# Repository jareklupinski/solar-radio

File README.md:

# solar-radio
A dev module for experimenting with low-power FM designs

The SI4825 is an interesting chip, so I made an easy to interface board for prototyping a few ideas I had.

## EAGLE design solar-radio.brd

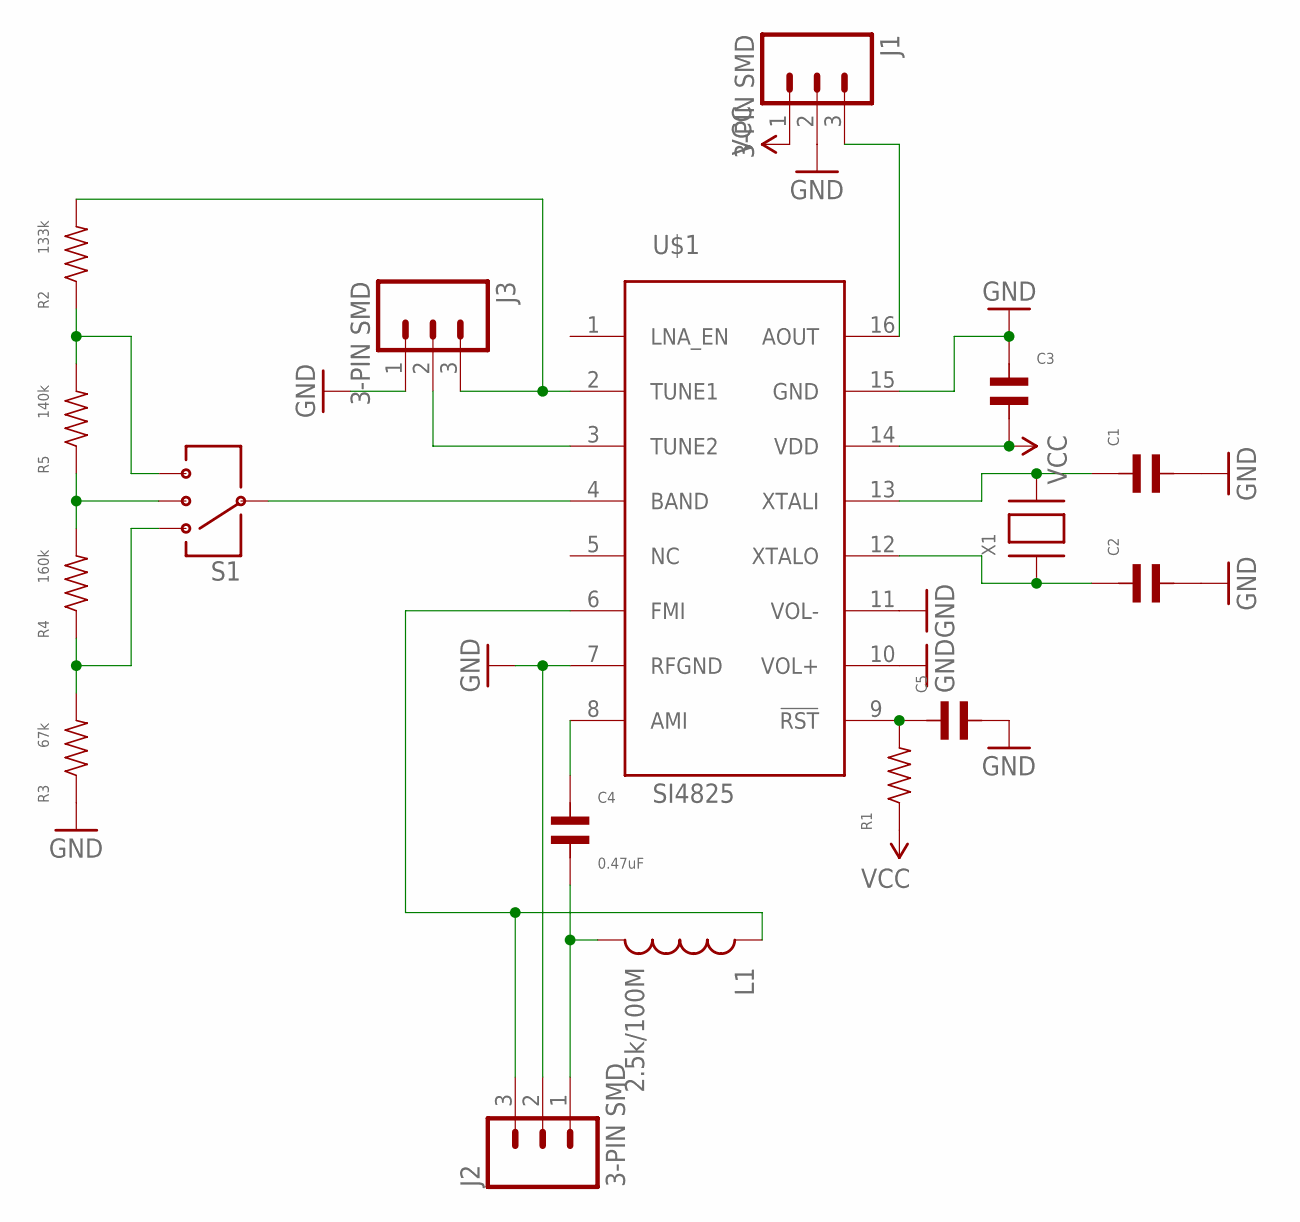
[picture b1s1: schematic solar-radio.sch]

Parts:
C1, C2, C3, C5: CAPACITOR_NP_0805; C0805
C4: 0.47uF; C0805
J1, J2, J3: 3-PIN SMD; JST-3-SMD
L1: 2.5k/100M; 0805
R1: RESISTOR_0805; R0805
R2: 133k; R0805
R3: 67k; R0805
R4: 160k; R0805
R5: 140k; R0805
S1: SWITCH-SP3T; SWITCH-SP3T-SMD
U$1: SI4825; SOIC16N
X1: XTAL-3.2X1.5; XTAL3215

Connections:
GND: C1.P$2, C2.P$2, C3.P$1, C5.P$2, J1.2, J2.2, J3.1, R3.P$1, U$1.7 (RFGND), U$1.10 (VOL+), U$1.11 (VOL-), U$1.15 (GND)
unnamed: J3.2, U$1.3 (TUNE2)
unnamed: J3.3, R2.P$2, U$1.2 (TUNE1)
unnamed: R2.P$1, R5.P$2, S1.4
unnamed: R4.P$2, R5.P$1, S1.2
unnamed: R3.P$2, R4.P$1, S1.1
unnamed: S1.3, U$1.4 (BAND)
unnamed: C4.P$1, U$1.8 (AMI)
unnamed: C4.P$2, J2.1, L1.2
unnamed: J2.3, L1.1, U$1.6 (FMI)
unnamed: C5.P$1, R1.P$2, U$1.9 (!RST)
unnamed: C1.P$1, U$1.13 (XTALI), X1.P$2
unnamed: C2.P$1, U$1.12 (XTALO), X1.P$1
unnamed: J1.3, U$1.16 (AOUT)
VCC: C3.P$2, J1.1, R1.P$1, U$1.14 (VDD)

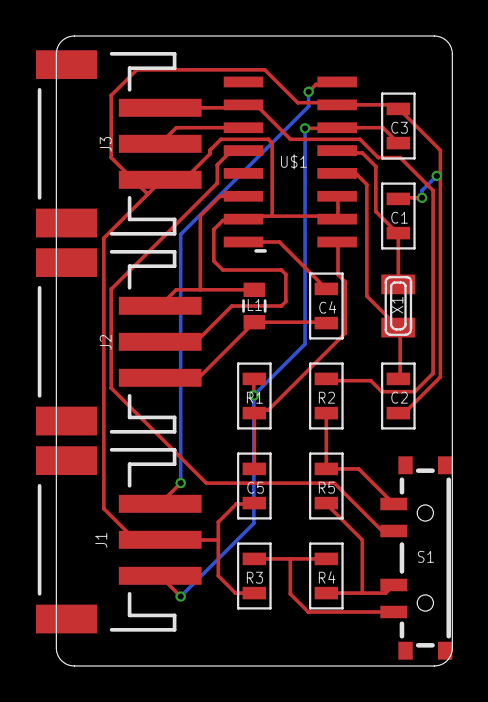
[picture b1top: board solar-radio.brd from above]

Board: 2 copper layers, 22.0 x 35.0 mm, 17 parts (0 on the bottom side), 15 nets.

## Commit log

2018-07-05 design untested

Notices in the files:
parts and their libraries:
SparkFun-Electromechanical: Licensing: Creative Commons ShareAlike 4.0 International - https://creativecommons.org/licenses/by-sa/4.0
